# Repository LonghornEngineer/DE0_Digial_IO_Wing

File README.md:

***
###DE0_Digial_IO_Wing
***
**Digital I/O Expansion Wing for the DE0 FPGA Development Board.**

This is for the [Altera DE0 Development Board by terasIC](http://www.terasic.com.tw/cgi-bin/page/archive.pl?Language=English&No=364). 

See [here for more information](http://longhornengineer.com/category/projects/hardware/de0-digital-io-wing-expansion/).

***
**License Information**

This project is under the [Creative Commons Attribution-ShareAlike 4.0 International License](LICENSE.md). These files are provided with no warranty and should be used at your own risk. 

***

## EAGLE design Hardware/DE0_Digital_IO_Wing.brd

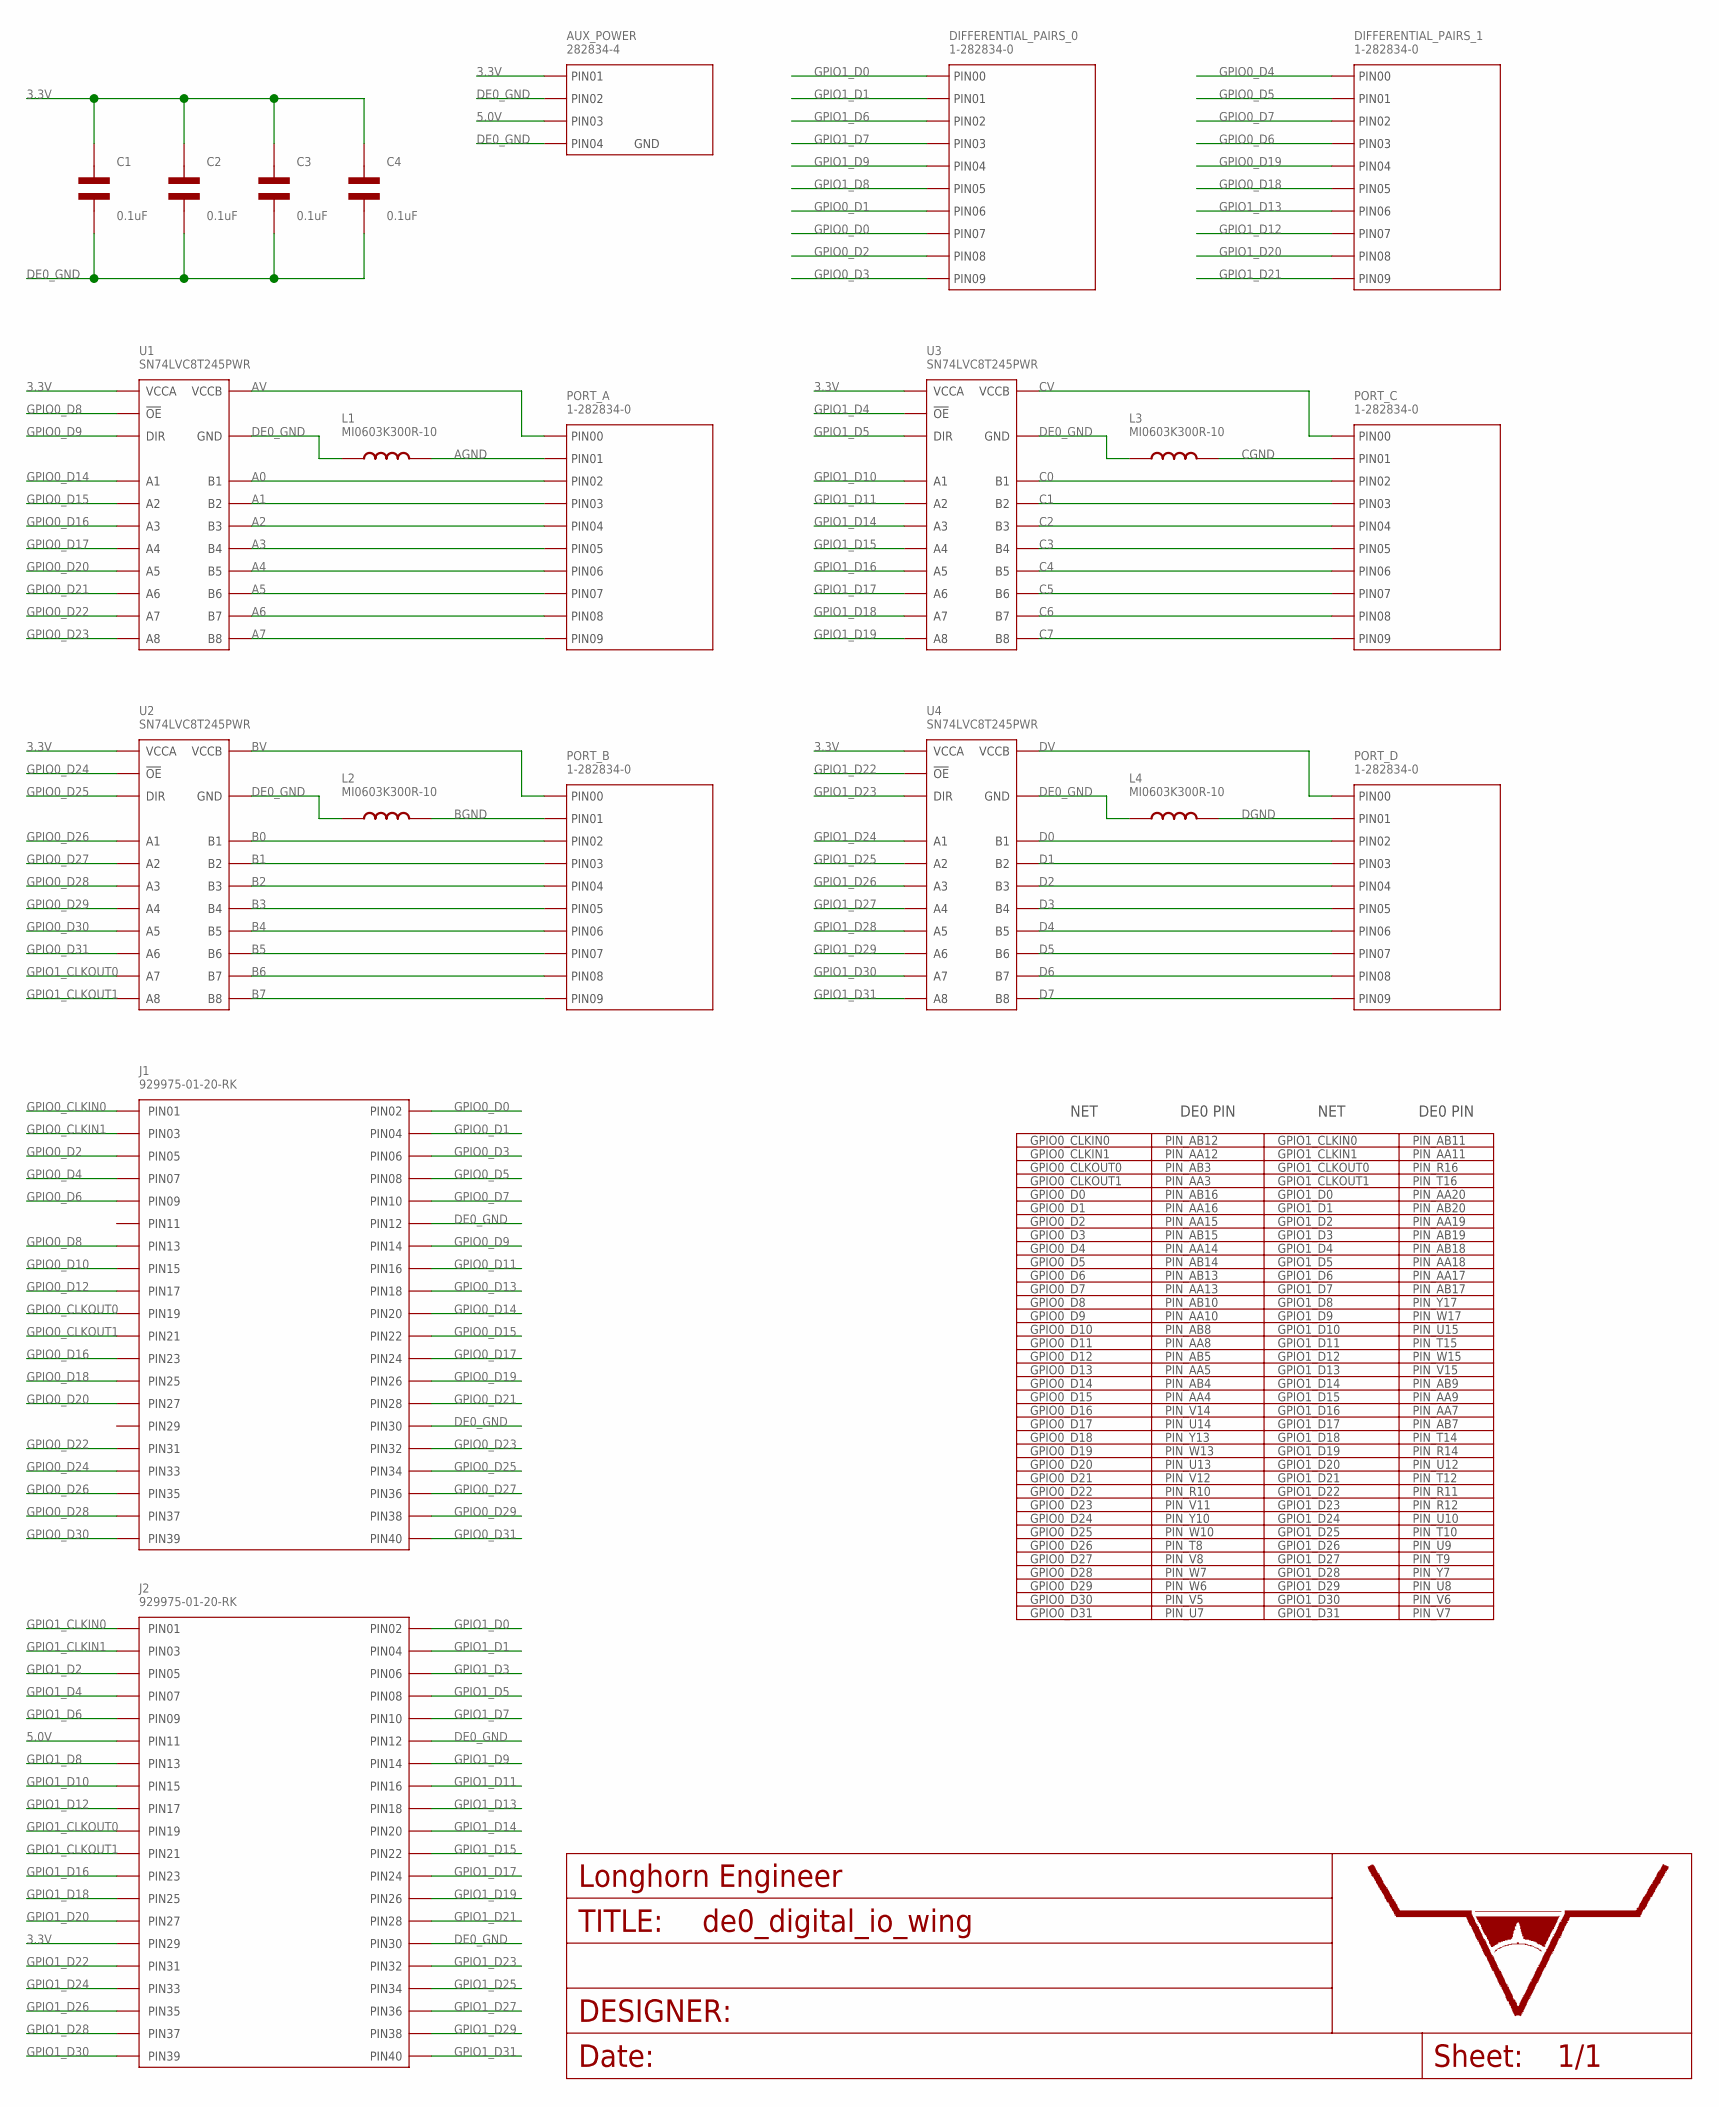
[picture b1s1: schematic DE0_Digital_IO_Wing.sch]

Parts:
AUX_POWER: 282834-4
C1, C2, C3, C4: 0.1uF; C0805
DIFFERENTIAL_PAIRS_0, DIFFERENTIAL_PAIRS_1: 1-282834-0
FRAME: LHE_FRAME
J1, J2: 929975-01-20-RK; 2.54MM_02X20_PIN_HEADER
L1, L2, L3, L4: MI0603K300R-10; L0603
PORT_A: 1-282834-0
PORT_B: 1-282834-0
PORT_C: 1-282834-0
PORT_D: 1-282834-0
U1, U2, U3, U4: SN74LVC8T245PWR; SN74LVC8T245_TTSOP-24

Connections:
3.3V: AUX_POWER.P$1 (1), C1.P$1, C2.P$1, C3.P$1, C4.P$1, J2.29, U1.P$1 (VCCA), U2.P$1 (VCCA), U3.P$1 (VCCA), U4.P$1 (VCCA)
5.0V: AUX_POWER.P$3 (3), J2.11
A0: PORT_A.P$3 (3), U1.P$21 (B1)
A1: PORT_A.P$4 (4), U1.P$20 (B2)
A2: PORT_A.P$5 (5), U1.P$19 (B3)
A3: PORT_A.P$6 (6), U1.P$18 (B4)
A4: PORT_A.P$7 (7), U1.P$17 (B5)
A5: PORT_A.P$8 (8), U1.P$16 (B6)
A6: PORT_A.P$9 (9), U1.P$15 (B7)
A7: PORT_A.P$10 (10), U1.P$14 (B8)
AGND: L1.P$2, PORT_A.P$2 (2)
AV: PORT_A.P$1 (1), U1.P$23 (VCCB), U1.P$24 (VCCB)
B0: PORT_B.P$3 (3), U2.P$21 (B1)
B1: PORT_B.P$4 (4), U2.P$20 (B2)
B2: PORT_B.P$5 (5), U2.P$19 (B3)
B3: PORT_B.P$6 (6), U2.P$18 (B4)
B4: PORT_B.P$7 (7), U2.P$17 (B5)
B5: PORT_B.P$8 (8), U2.P$16 (B6)
B6: PORT_B.P$9 (9), U2.P$15 (B7)
B7: PORT_B.P$10 (10), U2.P$14 (B8)
BGND: L2.P$2, PORT_B.P$2 (2)
BV: PORT_B.P$1 (1), U2.P$23 (VCCB), U2.P$24 (VCCB)
C0: PORT_C.P$3 (3), U3.P$21 (B1)
C1: PORT_C.P$4 (4), U3.P$20 (B2)
C2: PORT_C.P$5 (5), U3.P$19 (B3)
C3: PORT_C.P$6 (6), U3.P$18 (B4)
C4: PORT_C.P$7 (7), U3.P$17 (B5)
C5: PORT_C.P$8 (8), U3.P$16 (B6)
C6: PORT_C.P$9 (9), U3.P$15 (B7)
C7: PORT_C.P$10 (10), U3.P$14 (B8)
CGND: L3.P$2, PORT_C.P$2 (2)
CV: PORT_C.P$1 (1), U3.P$23 (VCCB), U3.P$24 (VCCB)
D0: PORT_D.P$3 (3), U4.P$21 (B1)
D1: PORT_D.P$4 (4), U4.P$20 (B2)
D2: PORT_D.P$5 (5), U4.P$19 (B3)
D3: PORT_D.P$6 (6), U4.P$18 (B4)
D4: PORT_D.P$7 (7), U4.P$17 (B5)
D5: PORT_D.P$8 (8), U4.P$16 (B6)
D6: PORT_D.P$9 (9), U4.P$15 (B7)
D7: PORT_D.P$10 (10), U4.P$14 (B8)
DE0_GND: AUX_POWER.P$2 (2), AUX_POWER.P$4 (4), C1.P$2, C2.P$2, C3.P$2, C4.P$2, J1.12, J1.30, J2.12, J2.30, L1.P$1, L2.P$1, L3.P$1, L4.P$1, U1.P$11 (GND), U1.P$12 (GND), U1.P$13 (GND), U2.P$11 (GND), U2.P$12 (GND), U2.P$13 (GND), U3.P$11 (GND), U3.P$12 (GND), U3.P$13 (GND), U4.P$11 (GND), U4.P$12 (GND), U4.P$13 (GND)
DGND: L4.P$2, PORT_D.P$2 (2)
DV: PORT_D.P$1 (1), U4.P$23 (VCCB), U4.P$24 (VCCB)
GPIO0_CLKIN0: J1.1
GPIO0_CLKIN1: J1.3
GPIO0_CLKOUT0: J1.19
GPIO0_CLKOUT1: J1.21
GPIO0_D0: DIFFERENTIAL_PAIRS_0.P$8 (8), J1.2
GPIO0_D1: DIFFERENTIAL_PAIRS_0.P$7 (7), J1.4
GPIO0_D2: DIFFERENTIAL_PAIRS_0.P$9 (9), J1.5
GPIO0_D3: DIFFERENTIAL_PAIRS_0.P$10 (10), J1.6
GPIO0_D4: DIFFERENTIAL_PAIRS_1.P$1 (1), J1.7
GPIO0_D5: DIFFERENTIAL_PAIRS_1.P$2 (2), J1.8
GPIO0_D6: DIFFERENTIAL_PAIRS_1.P$4 (4), J1.9
GPIO0_D7: DIFFERENTIAL_PAIRS_1.P$3 (3), J1.10
GPIO0_D8: J1.13, U1.P$22 (!OE)
GPIO0_D9: J1.14, U1.P$2 (DIR)
GPIO0_D10: J1.15
GPIO0_D11: J1.16
GPIO0_D12: J1.17
GPIO0_D13: J1.18
GPIO0_D14: J1.20, U1.P$3 (A1)
GPIO0_D15: J1.22, U1.P$4 (A2)
GPIO0_D16: J1.23, U1.P$5 (A3)
GPIO0_D17: J1.24, U1.P$6 (A4)
GPIO0_D18: DIFFERENTIAL_PAIRS_1.P$6 (6), J1.25
GPIO0_D19: DIFFERENTIAL_PAIRS_1.P$5 (5), J1.26
GPIO0_D20: J1.27, U1.P$7 (A5)
GPIO0_D21: J1.28, U1.P$8 (A6)
GPIO0_D22: J1.31, U1.P$9 (A7)
GPIO0_D23: J1.32, U1.P$10 (A8)
GPIO0_D24: J1.33, U2.P$22 (!OE)
GPIO0_D25: J1.34, U2.P$2 (DIR)
GPIO0_D26: J1.35, U2.P$3 (A1)
GPIO0_D27: J1.36, U2.P$4 (A2)
GPIO0_D28: J1.37, U2.P$5 (A3)
GPIO0_D29: J1.38, U2.P$6 (A4)
GPIO0_D30: J1.39, U2.P$7 (A5)
GPIO0_D31: J1.40, U2.P$8 (A6)
GPIO1_CLKIN0: J2.1
GPIO1_CLKIN1: J2.3
GPIO1_CLKOUT0: J2.19, U2.P$9 (A7)
GPIO1_CLKOUT1: J2.21, U2.P$10 (A8)
GPIO1_D0: DIFFERENTIAL_PAIRS_0.P$1 (1), J2.2
GPIO1_D1: DIFFERENTIAL_PAIRS_0.P$2 (2), J2.4
GPIO1_D2: J2.5
GPIO1_D3: J2.6
GPIO1_D4: J2.7, U3.P$22 (!OE)
GPIO1_D5: J2.8, U3.P$2 (DIR)
GPIO1_D6: DIFFERENTIAL_PAIRS_0.P$3 (3), J2.9
GPIO1_D7: DIFFERENTIAL_PAIRS_0.P$4 (4), J2.10
GPIO1_D8: DIFFERENTIAL_PAIRS_0.P$6 (6), J2.13
GPIO1_D9: DIFFERENTIAL_PAIRS_0.P$5 (5), J2.14
GPIO1_D10: J2.15, U3.P$3 (A1)
GPIO1_D11: J2.16, U3.P$4 (A2)
GPIO1_D12: DIFFERENTIAL_PAIRS_1.P$8 (8), J2.17
GPIO1_D13: DIFFERENTIAL_PAIRS_1.P$7 (7), J2.18
GPIO1_D14: J2.20, U3.P$5 (A3)
GPIO1_D15: J2.22, U3.P$6 (A4)
GPIO1_D16: J2.23, U3.P$7 (A5)
GPIO1_D17: J2.24, U3.P$8 (A6)
GPIO1_D18: J2.25, U3.P$9 (A7)
GPIO1_D19: J2.26, U3.P$10 (A8)
GPIO1_D20: DIFFERENTIAL_PAIRS_1.P$9 (9), J2.27
GPIO1_D21: DIFFERENTIAL_PAIRS_1.P$10 (10), J2.28
GPIO1_D22: J2.31, U4.P$22 (!OE)
GPIO1_D23: J2.32, U4.P$2 (DIR)
GPIO1_D24: J2.33, U4.P$3 (A1)
GPIO1_D25: J2.34, U4.P$4 (A2)
GPIO1_D26: J2.35, U4.P$5 (A3)
GPIO1_D27: J2.36, U4.P$6 (A4)
GPIO1_D28: J2.37, U4.P$7 (A5)
GPIO1_D29: J2.38, U4.P$8 (A6)
GPIO1_D30: J2.39, U4.P$9 (A7)
GPIO1_D31: J2.40, U4.P$10 (A8)

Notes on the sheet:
GPIO0_CLKIN0 GPIO0_CLKIN1 GPIO0_CLKOUT0 GPIO0_CLKOUT1 GPIO0_D0 GPIO0_D1 GPIO0_D2 GPIO0_D3 GPIO0_D4 GPIO0_D5 GPIO0_D6 GPIO0_D7 GPIO0_D8 GPIO0_D9 GPIO0_D10 GPIO0_D11 GPIO0_D12 GPIO0_D13 GPIO0_D14 GPIO0_D15 GPIO0_D16 GPIO0_D17 GPIO0_D18 GPIO0_D19 GPIO0_D20 GPIO0_D21 GPIO0_D22 GPIO0_D23 GPIO0_D24 GPIO0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
GPIO1_CLKIN0 GPIO1_CLKIN1 GPIO1_CLKOUT0 GPIO1_CLKOUT1 GPIO1_D0 GPIO1_D1 GPIO1_D2 GPIO1_D3 GPIO1_D4 GPIO1_D5 GPIO1_D6 GPIO1_D7 GPIO1_D8 GPIO1_D9 GPIO1_D10 GPIO1_D11 GPIO1_D12 GPIO1_D13 GPIO1_D14 GPIO1_D15 GPIO1_D16 GPIO1_D17 GPIO1_D18 GPIO1_D19 GPIO1_D20 GPIO1_D21 GPIO1_D22 GPIO1_D23 GPIO1_D24 GPIO1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
PIN_AB12 PIN_AA12 PIN_AB3 PIN_AA3 PIN_AB16 PIN_AA16 PIN_AA15 PIN_AB15 PIN_AA14 PIN_AB14 PIN_AB13 PIN_AA13 PIN_AB10 PIN_AA10 PIN_AB8 PIN_AA8 PIN_AB5 PIN_AA5 PIN_AB4 PIN_AA4 PIN_V14 PIN_U14 PIN_Y13 PIN_W13 PIN_U13 PIN_V12 PIN_R10 PIN_V11 PIN_Y10 PIN_W10 PIN_T8 PIN_V8 PIN_W7 PIN_W6 PIN_V5 PIN_U7
PIN_AB11 PIN_AA11 PIN_R16 PIN_T16 PIN_AA20 PIN_AB20 PIN_AA19 PIN_AB19 PIN_AB18 PIN_AA18 PIN_AA17 PIN_AB17 PIN_Y17 PIN_W17 PIN_U15 PIN_T15 PIN_W15 PIN_V15 PIN_AB9 PIN_AA9 PIN_AA7 PIN_AB7 PIN_T14 PIN_R14 PIN_U12 PIN_T12 PIN_R11 PIN_R12 PIN_U10 PIN_T10 PIN_U9 PIN_T9 PIN_Y7 PIN_U8 PIN_V6 PIN_V7
NET
DE0 PIN

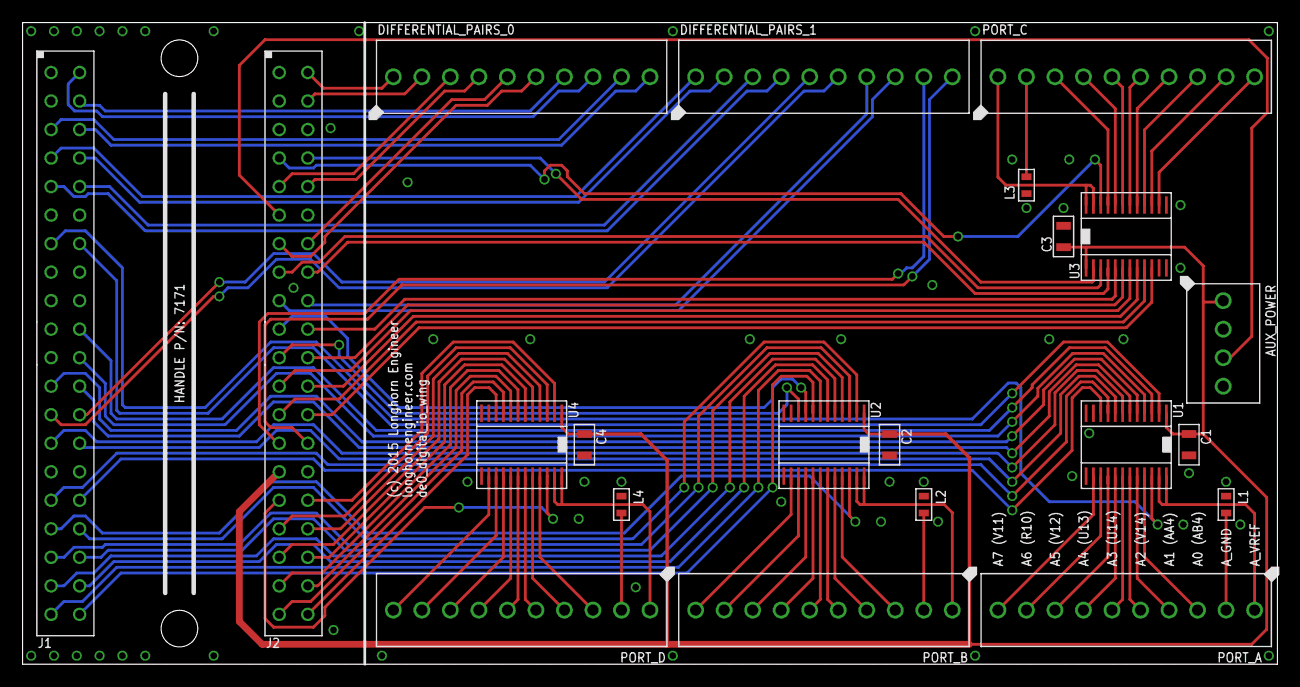
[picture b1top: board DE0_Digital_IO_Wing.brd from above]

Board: 2 copper layers, 111.8 x 57.1 mm, 22 parts (0 on the bottom side), 103 nets.

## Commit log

2015-01-27 First Commit. Adding Eagle files and Readme/License
2015-01-27 Quick fix for readmes
2015-02-02 Working on layout.
2015-02-08 REV0 preliminary complete.
2015-02-08 Fixed some traces crossing gnd planes.
2015-02-08 fixed silkscreen in some places.
2015-02-08 Fixed weird missing trace from Pin3 U1
2015-02-13 fixed silkscreen around ICs
2015-03-03 Adding first push of verilog code.
    Need to do pin planning and testing. Compiles tho. So there is that.
2015-12-14 Bringing it to current library spec.
2016-08-23 adding new readme info.

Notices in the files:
parts and their libraries:
PP_Aesthetics: (c) 2015 Longhorn Engineer
